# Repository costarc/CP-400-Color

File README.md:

# CP 400 Color

https://en.wikipedia.org/wiki/Prol%C3%B3gica_CP-400

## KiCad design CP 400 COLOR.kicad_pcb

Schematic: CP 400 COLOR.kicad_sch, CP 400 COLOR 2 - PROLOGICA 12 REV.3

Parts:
C1: 223; C_Axial_L3.8mm_D2.6mm_P7.50mm_Horizontal
C2: C2; C_Axial_L3.8mm_D2.6mm_P7.50mm_Horizontal
C3: C3; C_Axial_L3.8mm_D2.6mm_P7.50mm_Horizontal
C4: C4; C_Axial_L3.8mm_D2.6mm_P7.50mm_Horizontal
C5: C5; C_Axial_L3.8mm_D2.6mm_P7.50mm_Horizontal
C6: C6; C_Axial_L3.8mm_D2.6mm_P7.50mm_Horizontal
C7: 100uF; CP_Radial_Tantal_D10.5mm_P5.00mm
C8, C10, C15, C45: 104; C_Axial_L3.8mm_D2.6mm_P7.50mm_Horizontal
C8b1: 56pF; C_Axial_L3.8mm_D2.6mm_P7.50mm_Horizontal
C9: 560pF; C_Axial_L3.8mm_D2.6mm_P7.50mm_Horizontal
C12: C12; C_Axial_L3.8mm_D2.6mm_P7.50mm_Horizontal
C13: C13; C_Axial_L3.8mm_D2.6mm_P7.50mm_Horizontal
C14: C14; C_Axial_L3.8mm_D2.6mm_P7.50mm_Horizontal
C33: C33; C_Axial_L3.8mm_D2.6mm_P7.50mm_Horizontal
C34: C34; C_Axial_L3.8mm_D2.6mm_P7.50mm_Horizontal
C35: 10uf 25v; CP_Radial_Tantal_D10.5mm_P5.00mm
C36: 222; C_Axial_L3.8mm_D2.6mm_P7.50mm_Horizontal
C39, C40: 220; C_Axial_L3.8mm_D2.6mm_P7.50mm_Horizontal
C42: C42; C_Axial_L3.8mm_D2.6mm_P7.50mm_Horizontal
C44: 1Uf 100V; CP_Axial_L10.0mm_D4.5mm_P15.00mm_Horizontal
C49: 152; C_Axial_L3.8mm_D2.6mm_P7.50mm_Horizontal
C52: C52; C_Axial_L3.8mm_D2.6mm_P7.50mm_Horizontal
CH2: CANAL; PinHeader_1x03_P2.54mm_Horizontal
CI-1: 1372; DIP-14_W7.62mm
CI-2: 74LS244; DIP-20_W7.62mm
CI-3, CI-4, CI-5, CI-6, CI-7, CI-8, CI-9, CI-10: 4164; DIP-16_W7.62mm
CI-11, CI-12: 2764; DIP-28_W15.24mm
CI-13: MC6809E; DIP-40_W15.24mm
CI-14, CI-17: MC6821; DIP-40_W15.24mm
CI-15: 14529; DIP-16_W7.62mm
CI-16: LM339; DIP-14_W7.62mm
CI-18: CD4050BCN; DIP-16_W7.62mm
CI-19, CI-23: UA710CP; DIP-8_W7.62mm
CI-20: LM741; DIP-8_W7.62mm
CI-21: 74LS74; DIP-14_W7.62mm
CI-22: 74LS125; DIP-14_W7.62mm
CI-24: MC6847; DIP-40_W15.24mm
CI-27: 74LS123; DIP-16_W7.62mm
CI-28: 74LS138; DIP-16_W7.62mm
CI-29: MC6883; DIP-40_W15.24mm
CI-(3/4/5/6/7/8/9/10)1: 4164
CN1: CN9; PinHeader_1x03_P2.54mm_Vertical
CN2: CASSETE; PinHeader_1x05_P2.54mm_Vertical
CN3: CN8; PinHeader_1x03_P2.54mm_Vertical
CN4: RS232; PinHeader_1x04_P2.54mm_Vertical
CN5: JOYESQ; PinHeader_1x05_P2.54mm_Vertical
CN6: JOYDIR; PinHeader_1x05_P2.54mm_Vertical
CN7: CP400_CN7; PinHeader_1x05_P2.54mm_Vertical
CN8: CN12; PinHeader_1x03_P2.54mm_Vertical
CN10: CN10; PinHeader_1x03_P2.54mm_Vertical
CN13: CN13; PinHeader_1x13_P2.54mm_Vertical
CN14: CN14; PinHeader_1x13_P2.54mm_Vertical
CV-1: CV-1; C_Axial_L5.1mm_D3.1mm_P7.50mm_Horizontal
D1: D1; D_DO-34_SOD68_P7.62mm_Horizontal
D6: 1N4002; D_DO-34_SOD68_P7.62mm_Horizontal
D7: 1N4739; D_DO-34_SOD68_P7.62mm_Horizontal
D11: D11; D_DO-34_SOD68_P7.62mm_Horizontal
D12: D12; D_DO-34_SOD68_P7.62mm_Horizontal
D13, D15, D16, D17, D20, D21: 1N4148; D_DO-34_SOD68_P7.62mm_Horizontal
D14: 1N4148; D_DO-35_SOD27_P2.54mm_Vertical_AnodeUp
D18: D18; D_DO-34_SOD68_P7.62mm_Horizontal
D19: D19; D_DO-34_SOD68_P7.62mm_Horizontal
L2, L3: 3.3uh; L_Axial_L5.3mm_D2.2mm_P7.62mm_Horizontal_Vishay_IM-1
R1: R1; R_Axial_DIN0207_L6.3mm_D2.5mm_P7.62mm_Horizontal
R3: R3; R_Axial_DIN0207_L6.3mm_D2.5mm_P7.62mm_Horizontal
R4: R4; R_Axial_DIN0207_L6.3mm_D2.5mm_P7.62mm_Horizontal
R5: 470; R_Axial_DIN0207_L6.3mm_D2.5mm_P7.62mm_Horizontal
R6: R6; R_Axial_DIN0207_L6.3mm_D2.5mm_P7.62mm_Horizontal
R7: 360; R_Axial_DIN0207_L6.3mm_D2.5mm_P7.62mm_Horizontal
R8: R8; R_Axial_DIN0207_L6.3mm_D2.5mm_P7.62mm_Horizontal
R9: R9; R_Axial_DIN0207_L6.3mm_D2.5mm_P7.62mm_Horizontal
R10: 18K; R_Axial_DIN0207_L6.3mm_D2.5mm_P7.62mm_Horizontal
R11: R11; R_Axial_DIN0207_L6.3mm_D2.5mm_P7.62mm_Horizontal
R12: R12; R_Axial_DIN0207_L6.3mm_D2.5mm_P7.62mm_Horizontal
R13: R13; R_Axial_DIN0207_L6.3mm_D2.5mm_P7.62mm_Horizontal
R14: R14; R_Axial_DIN0207_L6.3mm_D2.5mm_P7.62mm_Horizontal
R20: R20; R_Axial_DIN0207_L6.3mm_D2.5mm_P7.62mm_Horizontal
R21: R21; R_Axial_DIN0207_L6.3mm_D2.5mm_P7.62mm_Horizontal
R22: R22; R_Axial_DIN0207_L6.3mm_D2.5mm_P2.54mm_Vertical
R23: R23; R_Axial_DIN0207_L6.3mm_D2.5mm_P7.62mm_Horizontal
R24: R24; R_Axial_DIN0207_L6.3mm_D2.5mm_P7.62mm_Horizontal
R25: R25; R_Axial_DIN0207_L6.3mm_D2.5mm_P7.62mm_Horizontal
R26: R26; R_Axial_DIN0207_L6.3mm_D2.5mm_P7.62mm_Horizontal
R27: R27; R_Axial_DIN0207_L6.3mm_D2.5mm_P7.62mm_Horizontal
R29: R29; R_Axial_DIN0207_L6.3mm_D2.5mm_P7.62mm_Horizontal
R30: R30; R_Axial_DIN0207_L6.3mm_D2.5mm_P7.62mm_Horizontal
R31: R31; R_Axial_DIN0207_L6.3mm_D2.5mm_P7.62mm_Horizontal
R32: R32; R_Axial_DIN0207_L6.3mm_D2.5mm_P7.62mm_Horizontal
R33: R33; R_Axial_DIN0207_L6.3mm_D2.5mm_P7.62mm_Horizontal
R34: 1.5K; R_Axial_DIN0207_L6.3mm_D2.5mm_P7.62mm_Horizontal
R35, R36: 100K; R_Axial_DIN0207_L6.3mm_D2.5mm_P7.62mm_Horizontal
R37: R37; R_Axial_DIN0207_L6.3mm_D2.5mm_P7.62mm_Horizontal
R38: R38; R_Axial_DIN0207_L6.3mm_D2.5mm_P7.62mm_Horizontal
R39: R39; R_Axial_DIN0207_L6.3mm_D2.5mm_P7.62mm_Horizontal
R40: R40; R_Axial_DIN0207_L6.3mm_D2.5mm_P7.62mm_Horizontal
R41: R41; R_Axial_DIN0207_L6.3mm_D2.5mm_P2.54mm_Vertical
R42: R42; R_Axial_DIN0207_L6.3mm_D2.5mm_P2.54mm_Vertical
R43: R43; R_Axial_DIN0207_L6.3mm_D2.5mm_P2.54mm_Vertical
R44: R44; R_Axial_DIN0207_L6.3mm_D2.5mm_P2.54mm_Vertical
R45: R45; R_Axial_DIN0207_L6.3mm_D2.5mm_P2.54mm_Vertical
R46: R46; R_Axial_DIN0207_L6.3mm_D2.5mm_P2.54mm_Vertical
R47: R47; R_Axial_DIN0207_L6.3mm_D2.5mm_P2.54mm_Vertical
R48: 7.5K; R_Axial_DIN0207_L6.3mm_D2.5mm_P2.54mm_Vertical
R49, R59: 4.7K; R_Axial_DIN0207_L6.3mm_D2.5mm_P2.54mm_Vertical
R50: 1.2K; R_Axial_DIN0207_L6.3mm_D2.5mm_P2.54mm_Vertical
R51: R51; R_Axial_DIN0207_L6.3mm_D2.5mm_P2.54mm_Vertical
R52: R52; R_Axial_DIN0207_L6.3mm_D2.5mm_P2.54mm_Vertical
R53: R53; R_Axial_DIN0207_L6.3mm_D2.5mm_P2.54mm_Vertical
R54: R54; R_Axial_DIN0207_L6.3mm_D2.5mm_P2.54mm_Vertical
R55: R55; R_Axial_DIN0207_L6.3mm_D2.5mm_P7.62mm_Horizontal
R56: R56; R_Axial_DIN0207_L6.3mm_D2.5mm_P7.62mm_Horizontal
R57: R57; R_Axial_DIN0207_L6.3mm_D2.5mm_P7.62mm_Horizontal
R58: R58; R_Axial_DIN0207_L6.3mm_D2.5mm_P7.62mm_Horizontal
R60: 3.3K; R_Axial_DIN0207_L6.3mm_D2.5mm_P2.54mm_Vertical
R61: R61; R_Axial_DIN0207_L6.3mm_D2.5mm_P7.62mm_Horizontal
R62: R62; R_Axial_DIN0207_L6.3mm_D2.5mm_P7.62mm_Horizontal
R63: R63; R_Axial_DIN0207_L6.3mm_D2.5mm_P7.62mm_Horizontal
R64: R64; R_Axial_DIN0207_L6.3mm_D2.5mm_P7.62mm_Horizontal
R65: R65; R_Axial_DIN0207_L6.3mm_D2.5mm_P7.62mm_Horizontal
R66: R66; R_Axial_DIN0207_L6.3mm_D2.5mm_P7.62mm_Horizontal
R67: R67; R_Axial_DIN0207_L6.3mm_D2.5mm_P7.62mm_Horizontal
R68: R68; R_Axial_DIN0207_L6.3mm_D2.5mm_P7.62mm_Horizontal
R69: R69; R_Axial_DIN0207_L6.3mm_D2.5mm_P7.62mm_Horizontal
R70: R70; R_Axial_DIN0207_L6.3mm_D2.5mm_P7.62mm_Horizontal
R71: R71; R_Axial_DIN0207_L6.3mm_D2.5mm_P7.62mm_Horizontal
R72: R72; R_Axial_DIN0207_L6.3mm_D2.5mm_P7.62mm_Horizontal
R73: R73; R_Axial_DIN0207_L6.3mm_D2.5mm_P7.62mm_Horizontal
R74: R74; R_Axial_DIN0207_L6.3mm_D2.5mm_P7.62mm_Horizontal
R75: R75; R_Axial_DIN0207_L6.3mm_D2.5mm_P7.62mm_Horizontal
R76: 10K; R_Axial_DIN0207_L6.3mm_D2.5mm_P2.54mm_Vertical
RL1: DIPxx-1Axx-12x; Relay_StandexMeder_DIP_LowProfile
TR1: F2N3904EBC; TO-92
TR2: TR1; TO-92
XTAL1: 14,30244 Mhz; Crystal_AT310_D3.0mm_L10.0mm_Horizontal

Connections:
1: CI-16.12 (V-), CI-20.4 (V-)
2: CI-16.3 (V+), CI-19.8 (VCC+), CI-20.7 (V+), CI-23.8 (VCC+), CN1.3, R3.2
3: CI-13.40 (~HALT), R14.1
4: CI-13.2 (~NMI), R13.1
5: C44.1, CI-13.37 (~RESET), CI-14.34 (~RESET), CI-17.34 (~RESET), D17.2 (A), R36.1
6: C12.1, CI-13.34 (EIN), CI-14.25 (ENABLE), CI-17.25 (ENABLE), CI-29.14 (E), D20.1 (K)
7: C13.1, CI-13.35 (QIN), CI-29.13 (Q)
8: CI-17.18 (CB1)
9: C7.1, C10.1, CI-1.11 (VCC), CI-2.20 (VCC), CI-3.1 (VBB), CI-3.8 (VDD), CI-4.1 (VBB), CI-4.8 (VDD), CI-5.1 (VBB), CI-5.8 (VDD), CI-6.1 (VBB), CI-6.8 (VDD), CI-7.1 (VBB), CI-7.8 (VDD), CI-8.1 (VBB), CI-8.8 (VDD), CI-9.1 (VBB), CI-9.8 (VDD), CI-10.1 (VBB), CI-10.8 (VDD), CI-11.1 (VPP), CI-11.27 (~PGM), CI-11.28 (VCC), CI-12.1 (VPP), CI-12.27 (~PGM), CI-12.28 (VCC), CI-13.7 (VCC), CI-14.20 (VCC), CI-15.16 (VDD), CI-17.20 (VCC), CI-18.1, CI-21.10 (~S), CI-21.13 (~R), CI-21.14 (VCC), CI-22.14 (VCC), CI-24.17 (Vcc), CI-27.3 (Clr), CI-27.16 (VCC), CI-28.16 (VCC), CI-29.40 (Vcc), CN1.1, CN3.1, CN10.3, D1.1 (K), D16.1 (K), R4.1, R7.2, R11.2, R12.2, R13.2, R14.2, R20.1, R22.2, R25.2, R32.2, R35.2, R36.2, R37.1, R51.1, R54.1, R56.1, R58.2, R59.2, R60.1, R62.2, R65.2, R67.2, R70.2, R71.1, R73.1, R76.2, RL1.6
10: CI-2.16, CI-3.2 (D), CI-11.11 (D0), CI-12.11 (D0), CI-13.31 (D0), CI-14.33 (D0), CI-17.33 (D0), CI-(3/4/5/6/7/8/9/10)1.2 (CI-10_DI7)
11: CI-2.3, CI-4.2 (D), CI-11.12 (D1), CI-12.12 (D1), CI-13.30 (D1), CI-14.32 (D1), CI-17.32 (D1), CI-(3/4/5/6/7/8/9/10)1.2 (CI-10_DI7)
12: CI-2.14, CI-5.2 (D), CI-11.13 (D2), CI-12.13 (D2), CI-13.29 (D2), CI-14.31 (D2), CI-17.31 (D2), CI-(3/4/5/6/7/8/9/10)1.2 (CI-10_DI7)
13: CI-2.5, CI-6.2 (D), CI-11.15 (D3), CI-12.15 (D3), CI-13.28 (D3), CI-14.30 (D3), CI-17.30 (D3), CI-(3/4/5/6/7/8/9/10)1.2 (CI-10_DI7)
14: CI-2.12 (O3a), CI-7.2 (D), CI-11.16 (D4), CI-12.16 (D4), CI-13.27 (D4), CI-14.29 (D4), CI-17.29 (D4), CI-(3/4/5/6/7/8/9/10)1.2 (CI-10_DI7)
15: CI-2.7, CI-8.2 (D), CI-11.17 (D5), CI-12.17 (D5), CI-13.26 (D5), CI-14.28 (D5), CI-17.28 (D5), CI-(3/4/5/6/7/8/9/10)1.2 (CI-10_DI7)
16: CI-2.18, CI-9.2 (D), CI-11.18 (D6), CI-12.18 (D6), CI-13.25 (D6), CI-14.27 (D6), CI-17.27 (D6), CI-(3/4/5/6/7/8/9/10)1.2 (CI-10_DI7)
17: CI-2.9, CI-10.2 (D), CI-11.19 (D7), CI-12.19 (D7), CI-13.24 (D7), CI-14.26 (D7), CI-17.26 (D7), CI-(3/4/5/6/7/8/9/10)1.2 (CI-10_DI7)
18: CI-13.32 (R/~W), CI-14.21 (R/~W), CI-17.21 (R/~W), CI-29.15 (R/W), D21.1 (K)
19: CI-3.5 (A0), CI-4.5 (A0), CI-5.5 (A0), CI-6.5 (A0), CI-7.5 (A0), CI-8.5 (A0), CI-9.5 (A0), CI-10.5 (A0), CI-11.10 (A0), CI-12.10 (A0), CI-13.23 (A0), CI-17.36 (RS0), CI-29.16 (A0)
20: CI-3.6 (A1), CI-4.6 (A1), CI-5.6 (A1), CI-6.6 (A1), CI-7.6 (A1), CI-8.6 (A1), CI-9.6 (A1), CI-10.6 (A1), CI-11.9 (A1), CI-12.9 (A1), CI-13.22 (A1), CI-17.35 (RS1), CI-29.17 (A1)
21: CI-3.7 (A2), CI-4.7 (A2), CI-5.7 (A2), CI-6.7 (A2), CI-7.7 (A2), CI-8.7 (A2), CI-9.7 (A2), CI-10.7 (A2), CI-11.8 (A2), CI-12.8 (A2), CI-13.21 (A2), CI-29.18 (A2)
22: CI-3.12 (A3), CI-4.12 (A3), CI-5.12 (A3), CI-6.12 (A3), CI-7.12 (A3), CI-8.12 (A3), CI-9.12 (A3), CI-10.12 (A3), CI-11.7 (A3), CI-12.7 (A3), CI-13.20 (A3), CI-29.19 (A3)
23: CI-3.11 (A4), CI-4.11 (A4), CI-5.11 (A4), CI-6.11 (A4), CI-7.11 (A4), CI-8.11 (A4), CI-9.11 (A4), CI-10.11 (A4), CI-11.6 (A4), CI-12.6 (A4), CI-13.19 (A4), CI-29.21 (A4)
24: CI-3.10 (A5), CI-4.10 (A5), CI-5.10 (A5), CI-6.10 (A5), CI-7.10 (A5), CI-8.10 (A5), CI-9.10 (A5), CI-10.10 (A5), CI-11.5 (A5), CI-12.5 (A5), CI-13.18 (A5), CI-29.22 (A5)
25: CI-11.4 (A6), CI-12.4 (A6), CI-13.17 (A6), CI-29.23 (A6)
26: CI-11.3 (A7), CI-12.3 (A7), CI-13.16 (A7), CI-29.24 (A7)
27: CI-11.25 (A8), CI-12.25 (A8), CI-13.15 (A8), CI-29.4 (A8)
28: CI-11.24 (A9), CI-12.24 (A9), CI-13.14 (A9), CI-29.3 (A9)
29: CI-11.21 (A10), CI-12.21 (A10), CI-13.13 (A10), CI-29.2 (A10)
30: CI-11.23 (A11), CI-12.23 (A11), CI-13.12 (A11), CI-29.1 (A11)
31: CI-11.2 (A12), CI-12.2 (A12), CI-13.11 (A12), CI-29.39 (A12)
32: CI-28.12 (Y3)
33: C1.1, C2.2, C3.2, C4.2, C5.2, C6.2, C7.2, C8.2, C9.2, C10.2, C12.2, C13.2, C14.2, C33.2, C34.2, C36.2, C39.2, C40.2, C42.2, C44.2, C45.2, C52.2, CH2.3, CI-1.4 (GND), CI-2.10 (GND), CI-3.16, CI-4.16, CI-5.16, CI-6.16, CI-7.16, CI-8.16, CI-9.16, CI-10.16, CI-11.14 (GND), CI-11.20 (~CE), CI-12.14 (GND), CI-12.20 (~CE), CI-13.1 (VSS), CI-13.39 (TSC), CI-14.1 (VSS), CI-15.8 (VSS), CI-15.11 (Y3), CI-17.1 (VSS), CI-18.8, CI-19.1 (GND), CI-21.1 (~R), CI-21.2 (D), CI-21.3 (C), CI-21.7 (GND), CI-22.7 (GND), CI-23.1 (GND), CI-24.1 (GND), CI-27.1 (A), CI-27.8 (GND), CI-28.5 (G2B), CI-28.8 (GND), CI-29.20 (GND), CI-(3/4/5/6/7/8/9/10)1.16 (GND), CN2.4, CN4.2, CN5.3, CN6.3, CN7.5, CN13.11, CV-1.2, D7.2 (A), D11.2 (A), D12.2 (A), R1.1, R10.1, R21.2, R24.1, R31.1, R33.1, R40.2, R52.2, R53.2, R63.1, R64.1, R68.1, R69.1, R74.2, TR2.1 (E)
35: CI-15.12 (Y2)
36: CI-28.7 (Y7), CI-28.9 (Y6)
37: CI-13.10 (A13), CI-29.38 (A13)
38: CI-13.9 (A14), CI-29.37 (A14)
39: CI-13.8 (A15), CI-29.36 (A15)
40: CI-28.6 (G1), R62.1
-5V: CI-19.4 (VCC-), CI-23.4 (VCC-), CN3.3
/DA0: CI-24.22 (DA0), CI-29.8 (DA0)
/RS0: CI-14.35 (RS1)
/RS1: CI-14.36 (RS0)
/VCLK: CI-29.7 (VClk), D15.2 (A), R5.2
//HS: CI-14.40 (CA1), CI-21.11 (C), CI-24.38 (/HS), CI-27.2 (B), CI-29.9 (/HS)
//WE: CI-29.10 (/WE), CI-(3/4/5/6/7/8/9/10)1.3 (/WR)
CN3-1: CN7.3, R30.2, R31.2
CN3-3: C14.1, C52.1, CI-1.6 (CHB), CI-24.9 (CHB), R61.2
CN3-4: CI-1.5 (0B), CI-24.10 (0B)
CN3-5: CI-19.3 (IN-), CI-23.2 (IN+), CI-24.11 (0A)
CN3-6: CI-1.9 (Y), CI-24.28 (Y)
CN10-A7: CI-3.9 (VCC), CI-4.9 (VCC), CI-5.9 (VCC), CI-6.9 (VCC), CI-7.9 (VCC), CI-8.9 (VCC), CI-9.9 (VCC), CI-10.9 (VCC), CI-(3/4/5/6/7/8/9/10)1.9 (A7/+5V), CN10.2
CN13-2: CI-14.13 (PB3), CN13.2
CN13-3: CI-14.11 (PB1), CN13.3, CN14.1
CN13-4: CI-14.14 (PB4), CN13.4
CN13-5: CI-14.15 (PB5), CN13.5
CN13-6: CI-14.16 (PB6), CN13.6
CN13-7: CI-14.12 (PB2), CN13.1, CN13.7
CN13-8: CI-14.10 (PB0), CN13.8, CN14.9
CN13-10: CI-14.17 (PB7), CN8.3, CN13.10
CNI13-9: C45.1, CN13.9, D15.1 (K), D16.2 (A), D17.1 (K), R35.1
CNI14-2: CI-14.6 (PA4), CN14.2
CNI14-3: CI-14.7 (PA5), CN14.3
CNI14-4: CI-14.2 (PA0), CN14.4, CN14.7, L2.1
CNI14-5: CI-14.5 (PA3), CN14.5
CNI14-6: CI-14.4 (PA2), CN14.6
CNI14-10: CI-14.3 (PA1), CN14.10, L3.1
CNI14-11: CI-14.8 (PA6), CN14.11
HI: CI-14.22 (CS0), CI-14.24 (CS1), CI-15.1 (STX), CI-17.22 (CS0), CI-17.24 (CS1), CN8.1, R25.1
JOYIN: CI-14.9 (PA7), CI-16.14, R71.2, R72.2
unnamed: C1.2, C35.2, CN2.2, R39.2, R40.1
unnamed: C2.1, CI-15.5 (X3), CN5.4
unnamed: C3.1, CI-15.4 (X2), CN5.5
unnamed: C4.1, CI-15.2 (X0), CN6.5
unnamed: C5.1, CI-15.3 (X1), CN6.4
unnamed: C6.1, CN5.1, CN6.1, R4.2
unnamed: C8.1, C8b1.2, CH2.1, CN7.2, D7.1 (K), R3.1, R8.2, TR1.3 (C)
unnamed: C8b1.1, R9.2, R10.2, TR1.2 (B)
unnamed: C9.1, CI-1.2 (OSCIn), CI-24.33 (Clk), R5.1
unnamed: C15.1, R6.1
unnamed: C15.2, CI-1.8 (CMO)
unnamed: C33.1, CN6.2, L2.2
unnamed: C34.1, CN5.2, L3.2
unnamed: C35.1, CI-15.13 (Y1), D11.1 (K), R20.2, R21.1
unnamed: C36.1, CN2.1, R23.2, R24.2
unnamed: C39.1, CI-29.5 (OscIn), XTAL1.1
unnamed: C40.1, R34.2, XTAL1.2
unnamed: C42.1, CI-15.14 (Y0), CI-16.8 (-), R22.1, R23.1, R41.2, R42.2, R43.2, R44.2, R45.2, R46.2
unnamed: C49.1, CI-27.15 (RCext), R60.2
unnamed: C49.2, CI-27.14 (Cext)
unnamed: CH2.2, CN7.4
unnamed: CI-1.7 (0A), D14.2 (A), R47.2, R61.1
unnamed: CI-1.10 (CHI), R6.2
unnamed: CI-1.12 (RFOut), R8.1, R9.1
unnamed: CI-1.13 (RFT), D6.2 (A), R7.1
unnamed: CI-1.14 (RFT), D6.1 (K)
unnamed: CI-11.22 (~OE), CI-28.13 (Y2)
unnamed: CI-12.22 (~OE), CI-28.14 (Y1)
unnamed: CI-14.19 (CB2), CI-15.7 (B)
unnamed: CI-14.23 (~CS2), CI-28.11 (Y4)
unnamed: CI-14.39 (CA2), CI-15.6 (A)
unnamed: CI-15.9 (Z), R75.1
unnamed: CI-15.10 (W), R29.2, R30.1
unnamed: CI-15.15 (STY), CI-17.19 (CB2)
unnamed: CI-16.1, CI-17.10 (PB0), R65.1, R66.2
unnamed: CI-16.2, CI-17.40 (CA1), R57.2, R58.1
unnamed: CI-16.4 (-), D18.1 (K), R63.2
unnamed: CI-16.5 (+), R57.1, R69.2, R70.1
unnamed: CI-16.6 (-), D19.1 (K), R64.2
unnamed: CI-16.7 (+), R66.1, R67.1, R68.2
unnamed: CI-16.9 (+), R72.1, R75.2
unnamed: CI-16.10 (-), R37.2, R38.1
unnamed: CI-16.11 (+), R55.2, R73.2, R74.1
unnamed: CI-16.13, CI-17.2 (PA0), R55.1, R56.2
unnamed: CI-17.3 (PA1), CI-20.2 (-)
unnamed: CI-17.4 (PA2), CI-18.9
unnamed: CI-17.5 (PA3), CI-18.11
unnamed: CI-17.6 (PA4), CI-18.14
unnamed: CI-17.7 (PA5), CI-18.7
unnamed: CI-17.8 (PA6), CI-18.5
unnamed: CI-17.9 (PA7), CI-18.3
unnamed: CI-17.11 (PB1), R29.1
unnamed: CI-17.12 (PB2), CN8.2
unnamed: CI-17.13 (PB3), CI-24.39 (CSS)
unnamed: CI-17.14 (PB4), CI-24.30 (GM0), CI-24.31 (/INT_EXT)
unnamed: CI-17.15 (PB5), CI-24.29 (GM1)
unnamed: CI-17.16 (PB6), CI-24.27 (GM2)
unnamed: CI-17.17 (PB7), CI-24.35 (/AG)
unnamed: CI-17.23 (~CS2), CI-28.10 (Y5)
unnamed: CI-17.39 (CA2), R26.1
unnamed: CI-18.2, R44.1
unnamed: CI-18.4, R41.1
unnamed: CI-18.6, R45.1
unnamed: CI-18.10, R43.1
unnamed: CI-18.12, R46.1
unnamed: CI-18.15, R42.1
unnamed: CI-19.2 (IN+), R53.1, R54.2
unnamed: CI-19.7 (OUT), CI-22.13
unnamed: CI-20.3 (+), R32.1, R33.2
unnamed: CI-20.6, R27.1
unnamed: CI-21.4 (~S), CI-22.3, R59.1
unnamed: CI-21.5 (Q), CI-28.4 (G2A)
unnamed: CI-21.9 (Q), CI-22.5
unnamed: CI-21.8 (~Q), CI-21.12 (D), CI-22.9, CI-22.12
unnamed: CI-22.1, CI-28.3 (C), CI-29.25 (S2)
unnamed: CI-22.2, D20.2 (A), D21.2 (A), R76.1
unnamed: CI-22.4, CI-23.7 (OUT)
unnamed: CI-22.8, R48.1, R50.1
unnamed: CI-22.10, CI-27.4 (~Q)
unnamed: CI-22.6, CI-22.11, D13.2 (A), R47.1, R48.2, R49.1
unnamed: CI-23.3 (IN-), R51.2, R52.1
unnamed: CI-28.1 (A), CI-29.27 (S0)
unnamed: CI-28.2 (B), CI-29.26 (S1)
unnamed: CI-29.6 (OscOut), R34.1
unnamed: CI-29.35 (MA7), CN10.1
unnamed: CI-(3/4/5/6/7/8/9/10)1.1 (NC), CN3.2
unnamed: CI-29.28 (MA0), CI-(3/4/5/6/7/8/9/10)1.5 (A0)
unnamed: CI-29.30 (MA2), CI-(3/4/5/6/7/8/9/10)1.6 (A2)
unnamed: CI-29.29 (MA1), CI-(3/4/5/6/7/8/9/10)1.7 (A1)
unnamed: CI-(3/4/5/6/7/8/9/10)1.8 (VCC), CN1.2
unnamed: CI-29.33 (MA5), CI-(3/4/5/6/7/8/9/10)1.10 (A5)
unnamed: CI-29.32 (MA4), CI-(3/4/5/6/7/8/9/10)1.11 (A4)
unnamed: CI-29.31 (MA3), CI-(3/4/5/6/7/8/9/10)1.12 (A3)
unnamed: CI-29.34 (MA6), CI-(3/4/5/6/7/8/9/10)1.13 (A6)
unnamed: CI-2.11, CI-24.34 (/AS), CI-24.40 (DD7), CI-(3/4/5/6/7/8/9/10)1.14 (CI-10_DO7)
unnamed: CI-2.2, CI-24.2 (DD6), CI-24.32 (INV), CI-(3/4/5/6/7/8/9/10)1.14 (CI-10_DO7)
unnamed: CI-2.6, CI-24.5 (DD2), CI-(3/4/5/6/7/8/9/10)1.14 (CI-10_DO7)
unnamed: CI-2.15, CI-24.6 (DD3), CI-(3/4/5/6/7/8/9/10)1.14 (CI-10_DO7)
unnamed: CI-2.4, CI-24.3 (DD0), CI-(3/4/5/6/7/8/9/10)1.14 (CI-10_DO7)
unnamed: CI-2.17, CI-24.4 (DD1), CI-(3/4/5/6/7/8/9/10)1.14 (CI-10_DO7)
unnamed: CI-2.13, CI-24.8 (DD5), CI-(3/4/5/6/7/8/9/10)1.14 (CI-10_DO7)
unnamed: CI-2.8 (I3a), CI-24.7 (DD4), CI-(3/4/5/6/7/8/9/10)1.14 (CI-10_DO7)
unnamed: CN2.3, RL1.1, RL1.14
unnamed: CN2.5, RL1.7, RL1.8
unnamed: CN4.1, R27.2
unnamed: CN4.3, D19.2 (A)
unnamed: CN4.4, D18.2 (A)
unnamed: CN7.1, R1.2, TR1.1 (E)
unnamed: D1.2 (A), RL1.2, RL1.13, TR2.3 (C)
unnamed: D12.1 (K), R38.2, R39.1
unnamed: D13.1 (K), R50.2
unnamed: D14.1 (K), R49.2
unnamed: R26.2, TR2.2 (B)
Q0: CI-3.14 (Q)
Q1: CI-4.14 (Q)
Q2: CI-5.14 (Q)
Q3: CI-6.14 (Q)
Q4: CI-7.14 (Q)
Q5: CI-8.14 (Q)
Q6: CI-9.14 (Q)
Q7: CI-10.14 (Q)
/CAS: CI-3.15 (/CAS), CI-4.15 (/CAS), CI-5.15 (/CAS), CI-6.15 (/CAS), CI-7.15 (/CAS), CI-8.15 (/CAS), CI-9.15 (/CAS), CI-10.15 (/CAS), CI-29.11 (/CAS), CI-(3/4/5/6/7/8/9/10)1.15 (/CAS)
/FIRQ: CI-13.4 (~FIRQ), CI-17.37 (~IRQB), CI-17.38 (~IRQA), R11.1
/FS: CI-14.18 (CB1), CI-24.12 (/MS), CI-24.37 (/FS)
/IRQ: CI-13.3 (~IRQ), CI-14.37 (~IRQB), CI-14.38 (~IRQA), R12.1
/MRD: CI-2.1 (OEa), CI-2.19 (OEb), CI-28.15 (Y0)
/RAS: CI-3.4 (/RAS), CI-4.4 (/RAS), CI-5.4 (/RAS), CI-6.4 (/RAS), CI-7.4 (/RAS), CI-8.4 (/RAS), CI-9.4 (/RAS), CI-10.4 (/RAS), CI-29.12 (/RAS), CI-(3/4/5/6/7/8/9/10)1.4 (/RAS)
/WR: CI-3.3 (R/W), CI-4.3 (R/W), CI-5.3 (R/W), CI-6.3 (R/W), CI-7.3 (R/W), CI-8.3 (R/W), CI-9.3 (R/W), CI-10.3 (R/W)

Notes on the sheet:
Removido no PCB Rev3
16K
RESET signal from Keyboard
Reset Circuit
32K
Added in Rev 3
CH 4
Requer Verificacao
16/4K
DRAM CIS 3 to 10 These are placed here to make it possible to assign the footprints for the 4164 RAMs
C8b1 nao esta no esquema original.
Precisa Confirmacao
Connector to Teclado. Esta versão do esquema visa utilizar o gabinete e teclado original do CP 400 Color. Por isso o esquema to teclado nao foi adicionado.

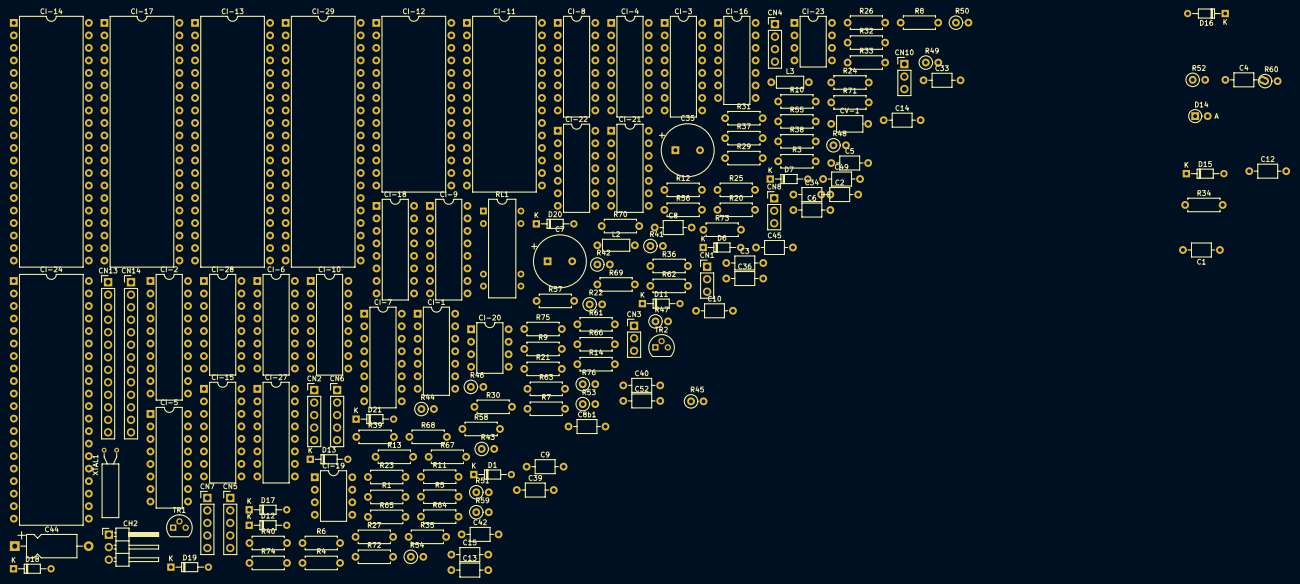
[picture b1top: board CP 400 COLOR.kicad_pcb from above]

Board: 2 copper layers, 155 parts (0 on the bottom side), 175 nets, no tracks yet.

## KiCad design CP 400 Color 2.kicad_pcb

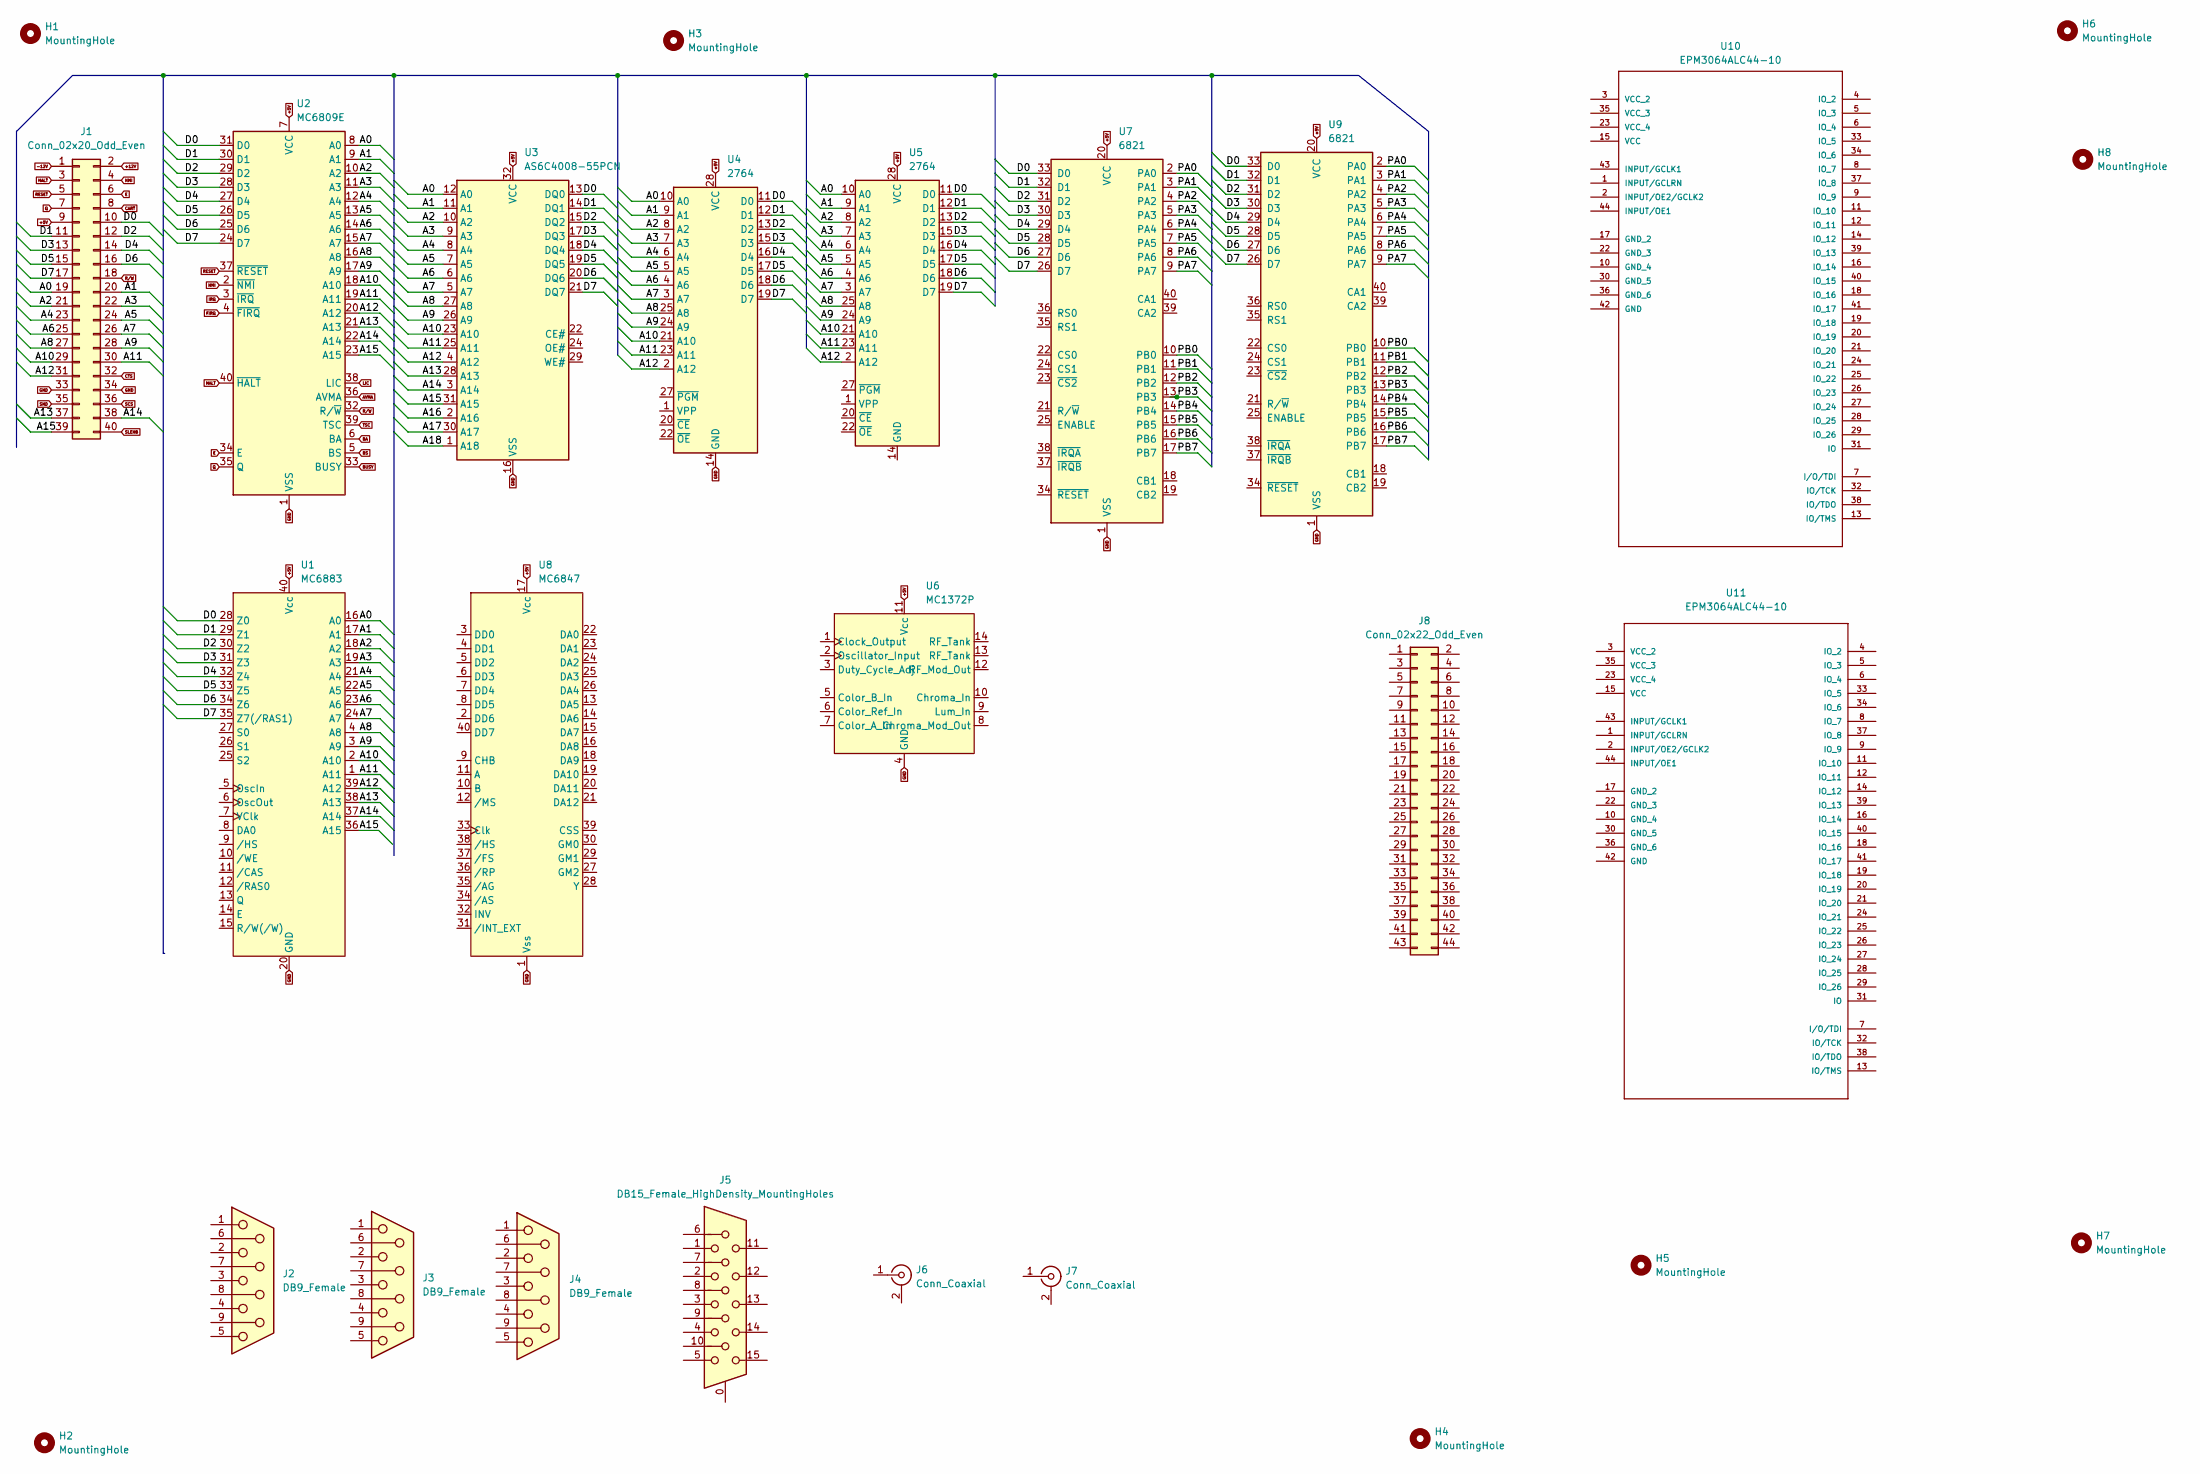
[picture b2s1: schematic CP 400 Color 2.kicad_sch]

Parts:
H1, H2, H4, H5, H6: MountingHole; MountingHole_3.2mm_M3
H3, H7, H8: MountingHole; MountingHole_6.5mm
J1: Conn_02x20_Odd_Even; IDC-Header_2x20_P2.54mm_Horizontal
J2, J3, J4: DB9_Female; DSUB-9_Female_Horizontal_P2.77x2.54mm_EdgePinOffset9.40mm
J5: DB15_Female_HighDensity_MountingHoles; DSUB-15_Female_Horizontal_P2.77x2.54mm_EdgePinOffset9.40mm
J6, J7: Conn_Coaxial; BarrelJack_CUI_PJ-063AH_Horizontal
J8: Conn_02x22_Odd_Even; IDC-Header_2x20_P2.54mm_Vertical
U1: MC6883; DIP-40_W15.24mm
U2: MC6809E; DIP-40_W15.24mm
U3: AS6C4008-55PCN; DIP-32_W15.24mm
U4, U5: 2764; DIP-28_W15.24mm
U6: MC1372P; DIP-14_W7.62mm
U7, U9: 6821; DIP-40_W15.24mm
U8: MC6847; DIP-40_W15.24mm
U10, U11: EPM3064ALC44-10; PLCC-44_THT-Socket

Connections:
+5V: J1.9, U1.40 (Vcc), U2.7 (VCC), U3.32 (VCC), U4.28 (VCC), U5.28 (VCC), U6.11 (Vcc), U7.20 (VCC), U8.17 (Vcc), U9.20 (VCC)
+12V: J1.2
-12V: J1.1
/A0: J1.19, U1.16 (A0), U2.8 (A0), U3.12 (A0), U4.10 (A0), U5.10 (A0)
/A1: J1.20, U1.17 (A1), U2.9 (A1), U3.11 (A1), U4.9 (A1), U5.9 (A1)
/A2: J1.21, U1.18 (A2), U2.10 (A2), U3.10 (A2), U4.8 (A2), U5.8 (A2)
/A3: J1.22, U1.19 (A3), U2.11 (A3), U3.9 (A3), U4.7 (A3), U5.7 (A3)
/A4: J1.23, U1.21 (A4), U2.12 (A4), U3.8 (A4), U4.6 (A4), U5.6 (A4)
/A5: J1.24, U1.22 (A5), U2.13 (A5), U3.7 (A5), U4.5 (A5), U5.5 (A5)
/A6: J1.25, U1.23 (A6), U2.14 (A6), U3.6 (A6), U4.4 (A6), U5.4 (A6)
/A7: J1.26, U1.24 (A7), U2.15 (A7), U3.5 (A7), U4.3 (A7), U5.3 (A7)
/A8: J1.27, U1.4 (A8), U2.16 (A8), U3.27 (A8), U4.25 (A8), U5.25 (A8)
/A9: J1.28, U1.3 (A9), U2.17 (A9), U3.26 (A9), U4.24 (A9), U5.24 (A9)
/A10: J1.29, U1.2 (A10), U2.18 (A10), U3.23 (A10), U4.21 (A10), U5.21 (A10)
/A11: J1.30, U1.1 (A11), U2.19 (A11), U3.25 (A11), U4.23 (A11), U5.23 (A11)
/A12: J1.31, U1.39 (A12), U2.20 (A12), U3.4 (A12), U4.2 (A12), U5.2 (A12)
/A13: J1.37, U1.38 (A13), U2.21 (A13), U3.28 (A13)
/A14: J1.38, U1.37 (A14), U2.22 (A14), U3.3 (A14)
/A15: J1.39, U1.36 (A15), U2.23 (A15), U3.31 (A15)
/A16: U3.2 (A16)
/A17: U3.30 (A17)
/A18: U3.1 (A18)
/D0: J1.10, U1.28 (Z0), U2.31 (D0), U3.13 (DQ0), U4.11 (D0), U5.11 (D0), U7.33 (D0), U9.33 (D0)
/D1: J1.11, U1.29 (Z1), U2.30 (D1), U3.14 (DQ1), U4.12 (D1), U5.12 (D1), U7.32 (D1), U9.32 (D1)
/D2: J1.12, U1.30 (Z2), U2.29 (D2), U3.15 (DQ2), U4.13 (D2), U5.13 (D2), U7.31 (D2), U9.31 (D2)
/D3: J1.13, U1.31 (Z3), U2.28 (D3), U3.17 (DQ3), U4.15 (D3), U5.15 (D3), U7.30 (D3), U9.30 (D3)
/D4: J1.14, U1.32 (Z4), U2.27 (D4), U3.18 (DQ4), U4.16 (D4), U5.16 (D4), U7.29 (D4), U9.29 (D4)
/D5: J1.15, U1.33 (Z5), U2.26 (D5), U3.19 (DQ5), U4.17 (D5), U5.17 (D5), U7.28 (D5), U9.28 (D5)
/D6: J1.16, U1.34 (Z6), U2.25 (D6), U3.20 (DQ6), U4.18 (D6), U5.18 (D6), U7.27 (D6), U9.27 (D6)
/D7: J1.17, U1.35 (Z7(/RAS1)), U2.24 (D7), U3.21 (DQ7), U4.19 (D7), U5.19 (D7), U7.26 (D7), U9.26 (D7)
/PA0: U7.2 (PA0), U9.2 (PA0)
/PA1: U7.3 (PA1), U9.3 (PA1)
/PA2: U7.4 (PA2), U9.4 (PA2)
/PA3: U7.5 (PA3), U9.5 (PA3)
/PA4: U7.6 (PA4), U9.6 (PA4)
/PA5: U7.7 (PA5), U9.7 (PA5)
/PA6: U7.8 (PA6), U9.8 (PA6)
/PA7: U7.9 (PA7), U9.9 (PA7)
/PB0: U7.10 (PB0), U9.10 (PB0)
/PB1: U7.11 (PB1), U9.11 (PB1)
/PB2: U7.12 (PB2), U9.12 (PB2)
/PB3: U7.13 (PB3), U9.13 (PB3)
/PB4: U7.14 (PB4), U9.14 (PB4)
/PB5: U7.15 (PB5), U9.15 (PB5)
/PB6: U7.16 (PB6), U9.16 (PB6)
/PB7: U7.17 (PB7), U9.17 (PB7)
AVMA: U2.36 (AVMA)
BA: U2.6 (BA)
BS: U2.5 (BS)
BUSY: U2.33 (BUSY)
CART: J1.8
CTS: J1.32
E: J1.6, U2.34 (E)
FIRQ: U2.4 (~FIRQ)
GND: J1.33, J1.34, U1.20 (GND), U2.1 (VSS), U3.16 (VSS), U4.14 (GND), U6.4 (GND), U7.1 (VSS), U8.1 (Vss), U9.1 (VSS)
HALT: J1.3, U2.40 (~HALT)
IRQ: U2.3 (~IRQ)
LIC: U2.38 (LIC)
NMI: J1.4, U2.2 (~NMI)
Q: J1.7, U2.35 (Q)
RESET: J1.5, U2.37 (~RESET)
R/W: J1.18, U2.32 (R/~W)
SCS: J1.36
SLENB: J1.40
SND: J1.35
TSC: U2.39 (TSC)

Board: 2 copper layers, 27 parts (0 on the bottom side), 48 nets, no tracks yet.

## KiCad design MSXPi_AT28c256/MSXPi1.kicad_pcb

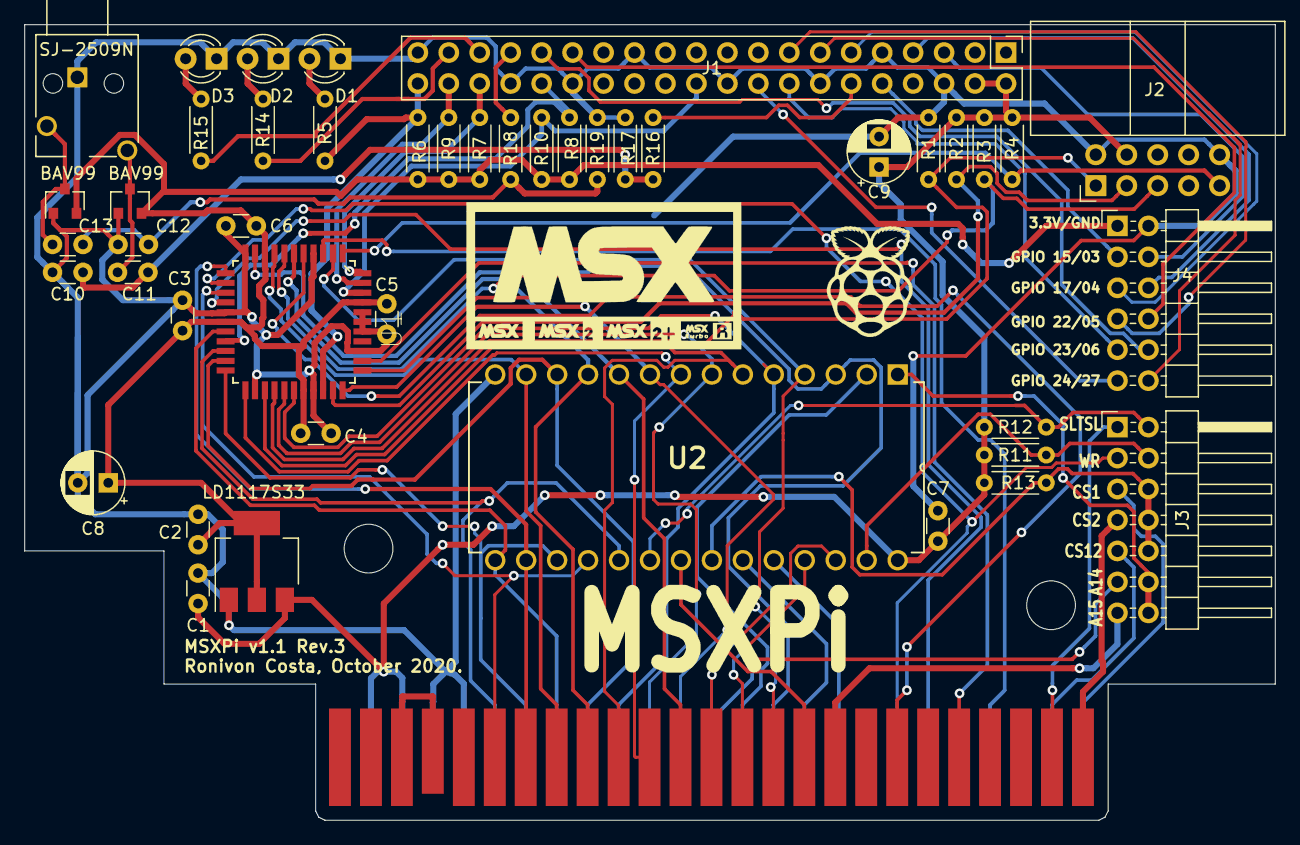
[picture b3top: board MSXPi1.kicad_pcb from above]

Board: 2 copper layers, 102.6 x 65.3 mm, 46 parts (0 on the bottom side), 71 nets.

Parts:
C1, C2, C3, C4, C5, C6, C7: 100nF; C_Disc_D3.0mm_W1.6mm_P2.50mm
C8, C9: 100uF; CP_Radial_D5.0mm_P2.50mm
C10, C12: 33nF; C_Disc_D3.0mm_W1.6mm_P2.50mm
C11, C13: 10uF; C_Disc_D3.0mm_W1.6mm_P2.50mm
D1, D2, D3: LED; LED_D3.0mm
D4, D5: BAV99; SOT-23
J1: J1 - Raspberry_Pi_Zero_2_3; PinHeader_2x20_P2.54mm_Vertical
J2: JTAG; IDC-Header_2x05_P2.54mm_Horizontal
J3: Conn_02x07_Odd_Even; PinHeader_2x07_P2.54mm_Horizontal
J4: Conn_02x06_Odd_Even; PinHeader_2x06_P2.54mm_Horizontal
J5: SJ-2509N; CUI_SJ-2509N
LD1117S33: LD1117S33TR_SOT223; SOT-223-3_TabPin2
P1: MSX_CONNECTOR; card_edge_connector
R1, R2, R3, R4: 1k; R_Axial_DIN0204_L3.6mm_D1.6mm_P5.08mm_Horizontal
R5, R14, R15, R16, R18: 270R; R_Axial_DIN0204_L3.6mm_D1.6mm_P5.08mm_Horizontal
R6, R7: 10K; R_Axial_DIN0204_L3.6mm_D1.6mm_P5.08mm_Horizontal
R8, R9, R10, R11, R12, R13: 10k; R_Axial_DIN0204_L3.6mm_D1.6mm_P5.08mm_Horizontal
R17, R19: 150R; R_Axial_DIN0204_L3.6mm_D1.6mm_P5.08mm_Horizontal
U1: EPM3064ATC44-10N; QFP80P1200X1200X120-44N
U2: AT28C256-15PU; DIP254P1524X482-28

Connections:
+3V3: C2.2, C3.2, C4.2, C5.2, C6.2, C8.1, D4.2, D5.2, J4.1, LD1117S33.2, R6.2, R7.2, R8.2, R9.2, R10.2, U1.9, U1.17, U1.29, U1.41
+5V: C1.1, C7.2, C9.1, J1.2, J1.4, J2.4, LD1117S33.3, P1.45, P1.47, R2.2, R3.2, R4.2, R11.2, R12.2, R13.2, U2.28
A0: P1.28, U1.34, U2.10
A1: P1.27, U1.33, U2.9
A2: P1.30, U1.23, U2.8
A3: P1.29, U1.27, U2.7
A4: P1.32, U1.25, U2.6
A5: P1.31, U1.28, U2.5
A6: P1.22, U1.2, U2.4
A7: P1.21, U1.10, U2.3
A8: P1.24, U2.25
A9: P1.17, U2.24
A10: P1.20, U2.21
A11: P1.19, U2.23
A12: P1.23, U2.2
A13: P1.26, U2.26
A14: J3.11, P1.25
A15: J3.13, P1.18
BUSDIR: P1.10, U1.35
CS1: J3.5, P1.1
CS2: J3.7, P1.2
CS12: J3.9, P1.3
D0: P1.34, U1.6, U2.11
D1: P1.33, U1.21, U2.12
D2: P1.36, U1.8, U2.13
D3: P1.35, U1.18, U2.15
D4: P1.38, U1.12, U2.16
D5: P1.37, U1.22, U2.17
D6: P1.40, U1.14, U2.18
D7: P1.39, U1.20, U2.19
GNDREF: C1.2, C2.1, C3.1, C4.1, C5.1, C6.1, C7.1, C8.2, C9.2, C10.1, C12.1, D1.1, D2.1, D3.1, D4.1, D5.1, J1.6, J1.9, J1.14, J1.20, J1.25, J1.30, J1.34, J1.39, J2.2, J2.10, J4.2, J5.1, LD1117S33.1, P1.41, P1.43, R1.1, R17.2, R19.2, U1.4, U1.11, U1.16, U1.24, U1.30, U1.36, U1.38, U1.39, U1.40, U2.14
GPIO3: J1.5, J4.4
GPIO4: J1.7, J4.6
GPIO5: J1.29, J4.8
GPIO6: J1.31, J4.10
GPIO15: J1.10, J4.3
GPIO17: J1.11, J4.5
GPIO22: J1.15, J4.7
GPIO23: J1.16, J4.9
GPIO24: J1.18, J4.11
GPIO27: J1.13, J4.12
IORQ: P1.11, U1.15
unnamed: C10.2, C11.2, R16.2, R17.1
unnamed: C11.1, D4.3, J5.3
unnamed: C12.2, C13.2, R18.2, R19.1
unnamed: C13.1, D5.3, J5.2
unnamed: D1.2, R5.1
unnamed: D2.2, R14.1
unnamed: D3.2, R15.1
unnamed: P1.44, P1.46
PWM0: J1.12, R16.1
PWM1: J1.33, R18.1
RD: P1.14, U1.5
ROM_A14: J3.12, J3.14, U2.1
RPI_BUSY: J1.35, R15.2
RPI_ON: J1.37, R14.2
SLTSL: J3.1, P1.4
SPI_CS: J1.40, R5.2, R6.1, U1.31
SPI_MISO: J1.32, R8.1, U1.19
SPI_MOSI: J1.36, R7.1, U1.44
SPI_RDY: J1.22, R10.1, U1.42
SPI_SCLK: J1.38, R9.1, U1.43
TCK: J2.1, R1.2, U1.26
TDI: J2.9, R4.1, U1.1
TDO: J2.3, R2.1, U1.32
TMS: J2.5, R3.1, U1.7
WAIT: P1.7, U1.3
WR: J3.3, P1.13, U1.13
mem_ce: J3.2, R12.1, U2.20
mem_oe: J3.6, J3.8, J3.10, R13.1, U2.22
mem_we: J3.4, R11.1, U2.27

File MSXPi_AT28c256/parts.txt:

R1		1K Ohm (THT Resistor 0.25W,3.5mm length)
R2		1k Ohm (THT Resistor 0.25W,3.5mm length)
R3		1k Ohm (THT Resistor 0.25W,3.5mm length)
R4		1k Ohm (THT Resistor 0.25W,3.5mm length)
R5		270 Ohm (THT Resistor 0.25W,3.5mm length)
R6		10k Ohm (THT Resistor 0.25W,3.5mm length)
R7		10K Ohm (THT Resistor 0.25W,3.5mm length)
R8		10k Ohm (THT Resistor 0.25W,3.5mm length)
R9		10k Ohm (THT Resistor 0.25W,3.5mm length)
R10		10k Ohm (THT Resistor 0.25W,3.5mm length)
R11		10k Ohm (THT Resistor 0.25W,3.5mm length)
R12		10k Ohm (THT Resistor 0.25W,3.5mm length)
R13		10k Ohm (THT Resistor 0.25W,3.5mm length)
R14		270 Ohm (THT Resistor 0.25W,3.5mm length)
R15		270 Ohm (THT Resistor 0.25W,3.5mm length)
R16		270 Ohm (THT Resistor 0.25W,3.5mm length)
R17		150 Ohm (THT Resistor 0.25W,3.5mm length)
R18		270 Ohm (THT Resistor 0.25W,3.5mm length)
R19		150 Ohm (THT Resistor 0.25W,3.5mm length)

D1		3mm, 3v (LED Blue)
D2		3mm, 3v (LED Green)
D3		3mm, 3v (LED Reed)
D4		BAV99 High speed switching diode (SMD SOT-23)
D5		BAV99 High speed switching diode (SMD SOT-23)

C1		100nF (ceramic capacitor, code 104)
C2		100nF (ceramic capacitor, code 104)
C3		100nF (ceramic capacitor, code 104)
C4		100nF (ceramic capacitor, code 104)
C5		100nF (ceramic capacitor, code 104)
C6		100nF (ceramic capacitor, code 104)
C7		100nF (ceramic capacitor, code 104)

C8		100uF 16v (electrolytic capacitor)
C9		100uF 16v (electrolytic capacitor)

C10		33nF (ceramic capacitor, code 333k)
C11		10uF(ceramic capacitor, code 106)
C12		33nF (ceramic capacitor, code 333k)
C13		10uF(ceramic capacitor, code 106)

U1		CPLD Altera EPM3064ATC44-10N (TQPF)
U2		EEPROM ATMEL AT28C256 (DIP-28)
U3		LD117AS33  3.3v Voltage Regulator
J1		Pin Header Female 2x20 Pins, 2.54mm, Vertical
J2		JTAG Connector - IDC Pin Header 2x05 pins, 2.54mm)
J3		Pin Header Male 2x07 Pins, 2.54mm, right angle
J4		Pin Header Male 2x06 Pins, 2.54mm, right angle
J5		SJ-2509N - 2.5MM Stereo Jack

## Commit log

2022-10-19 initial CP400 Color commit
2022-10-19 rebased & cleaned
2022-10-19 Added kicad artifacts to the branch
2022-10-19 no significant changes
2022-11-21 Added most of the CP 400 CIs to the schema. Added datasheets
2022-11-30 Progressing with schematic for Prologica 12 Rev.3 for CP 400 Color
2022-11-30 Added symbol 74ls183.
2022-12-01 more updates
2022-12-01 Added CP400_14529 and Joystick schema
2022-12-05 Continuing drawing schematic
2022-12-07 Reviewing but still incomplete schematic
2022-12-07 Confirmed connection from D21 to R/W
2022-12-08 Validated ci-19 & ci-24 (UA710CP) againts Rev.3 board
2022-12-08 some mroe revisioning done
2022-12-08 Doing revision; annotations completed
2022-12-11 Repositioned all mouting holes for the pcb to match the actual CP 400 mounting holes
2022-12-11 Mounting holes are final, looks to be in the precise locations for the CP 400 Color case.
2022-12-11 assigned some footprints
2022-12-11 Change page size to fit schematic
2022-12-12 Changed symbol for 74LS244 for better layouting
2022-12-13 Fixed VCLK signal not connected to MC1372P
2022-12-13 Added some component values, in what is promised to be a huge work ahead
2022-12-13 Updates to some more component values; added an C8b that was not in the schematic
2022-12-29 Added some components values; Added Photo with component identification in the PCB - WIP
2022-12-30 Updated PCB component layout (photography)
2023-01-05 Added pdf
2023-01-05 Schematic release. PCB routing not available
2023-02-09 Added video mod files to add to schematic
2023-02-09 Add video mods to the schematic
2023-02-09 Added video mod to the schematic - removed RF circuit
2023-02-09 Added coaxial connector for composite video
2023-02-10 changed pinout of din-7 for compatibility with cable in datassete.org
2023-02-10 Add more values to components
